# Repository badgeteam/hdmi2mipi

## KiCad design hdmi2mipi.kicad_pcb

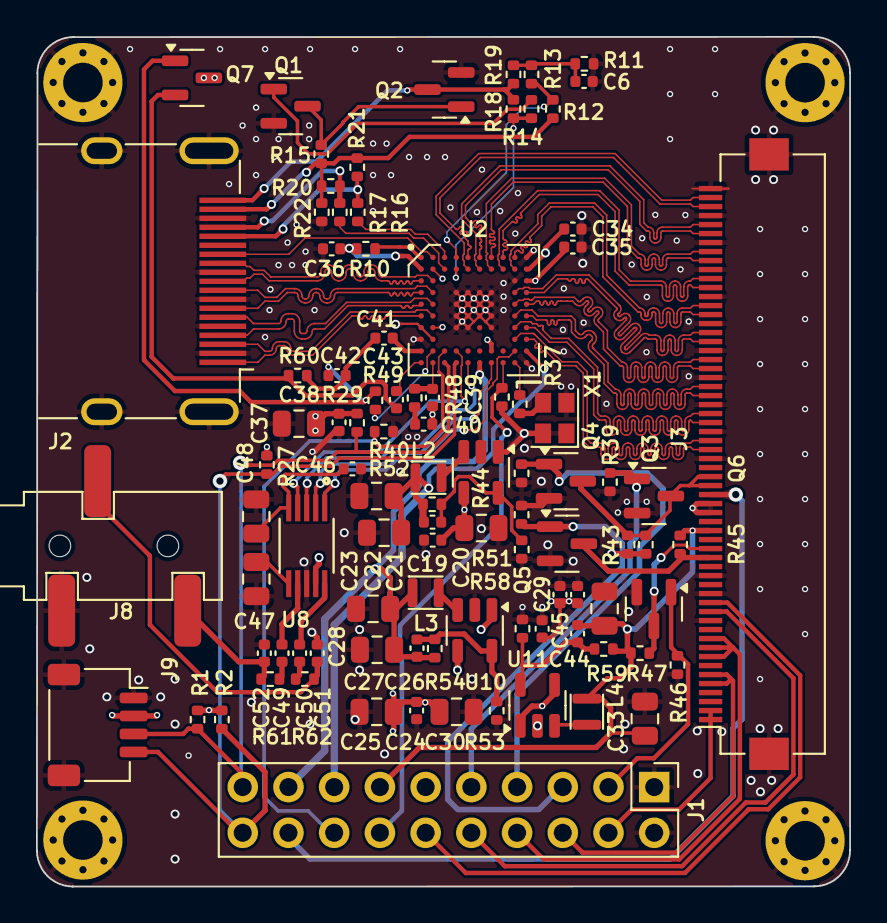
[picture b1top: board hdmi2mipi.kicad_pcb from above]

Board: 4 copper layers, 45.2 x 47.2 mm, 99 parts (0 on the bottom side), 91 nets.

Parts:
C6, C40, C41: 0.1u; C_0402_1005Metric
C19, C24, C29, C34, C35, C36, C38, C45, C46, C49, C50: 100n; C_0402_1005Metric
C20, C22, C23, C25, C27, C28, C30, C32, C33, C37: 22u; C_0805_2012Metric
C21, C26, C31: 22p; C_0402_1005Metric
C39, C43: 1n; C_0402_1005Metric
C42: 5p; C_0402_1005Metric
C44: 1u; C_0402_1005Metric
C47, C48: 47u; C_0805_2012Metric
C51, C52: 39n; C_0402_1005Metric
H1, H2, H3, H4: MountingHole_Pad; MountingHole_2.2mm_M2_Pad_Via
J1: IO; PinHeader_2x10_P2.54mm_Vertical
J2: HDMI_A_1.4; HDMI_A_Molex_208658-1001_Horizontal
J3: Hirose_FH52-60S-0.5SH_1x60-1MP_P0.50mm_Horizontal
J8: AudioJack3; Boom-audiojack-PJ-320B
J9: QWIIC; JST_SH_SM04B-SRSS-TB_1x04-1MP_P1.00mm_Horizontal
L2, L3, L4: 2.2u; Inductor_MSC20FC
Q1, Q2, Q3, Q4, Q5, Q6: BC846; SOT-23
Q7: 2SC2712; SOT-23
R1, R2, R10: 2k; R_0402_1005Metric
R11: 48k; R_0402_1005Metric
R12: 0; R_0402_1005Metric
R13, R49: 1.5k; R_0402_1005Metric
R14, R20, R21, R27, R29, R41, R43, R45, R47: 4.7k; R_0402_1005Metric
R15, R38, R39, R40, R42, R44, R46, R51, R52, R53, R58: 10k; R_0402_1005Metric
R16, R17, R37: 33; R_0402_1005Metric
R18, R19, R48, R60: 1k; R_0402_1005Metric
R22: 100k; R_0402_1005Metric
R54: 8.2k; R_0402_1005Metric
R59: 20k; R_0402_1005Metric
R61, R62: 330; R_0402_1005Metric
U2: tc358840xbg
U8: MS4344; SOP50P490X110-10N
U9, U10, U11: SY8079AAC; SOT-23-5
X1: SG-210STF; Oscillator_SMD_SeikoEpson_SG210-4Pin_2.5x2.0mm

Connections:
1V8_S1: J1.3, Q6.1 (B), R46.1
1V8_S2: J1.5, Q5.1 (B), R44.1
3V3_HDMI: C19.1, C20.1, C24.1, C25.1, C29.1, C30.1, C36.1, C37.1, C38.1, C44.1, C45.1, J1.11, J3.24 (3.3v), J3.25 (3.3v), J9.2, Q7.3 (C), R1.1, R2.1, R10.2, R27.1, R29.1, R38.1, R41.1, R43.1, U2.B1 (VDD33_HDMI), U2.G1 (VDD33_HDMI), U2.H2 (VDDIO33), U2.J7 (VDDIO18), U8.9 (VA), U9.1 (EN), U9.4 (VIN), U10.1 (EN), U10.4 (VIN), U11.1 (EN), U11.4 (VIN), X1.1 (~ST), X1.4 (Vcc)
3V3_S1: J1.7, Q4.1 (B), R42.1
3V3_S2: J1.9, Q3.1 (B), R39.1
+1V1: C26.1, C27.1, C28.1, C35.1, J1.17, L3.1, R54.1, U2.B2 (VDD11_HDMI), U2.C10 (VDDC11), U2.G2 (VDD11_HDMI), U2.K6 (VDDC11)
+1V2: C21.1, C22.1, C23.1, C34.1, J1.15, L2.1, R52.1, U2.B10 (VDD12_MIPI1), U2.J10 (VDD12_MIPI0)
+1V8: C31.1, C32.1, C33.1, J1.13, J3.22 (1.8v), L4.1, R45.1, R47.1, R59.1
/AUDIO_L: C52.2, J8.T, R61.2
/AUDIO_R: C51.2, J8.R, R62.2
/DSI0_C_N: J3.38 (DSI0CN), U2.F9 (CDSI0CN)
/DSI0_C_P: J3.37 (DSI0CP), U2.F10 (CDSI0CP)
/DSI0_D0_N: J3.32 (DSI0D0N), U2.H9 (CDSI0D0N)
/DSI0_D0_P: J3.31 (DSI0D0P), U2.H10 (CDSI0D0P)
/DSI0_D1_N: J3.35 (DSI0D1N), U2.G9 (CDSI0D1N)
/DSI0_D1_P: J3.34 (DSI0D1P), U2.G10 (CDSI0D1P)
/DSI0_D2_N: J3.41 (DSI0D2N), U2.E9 (CDSI0D2N)
/DSI0_D2_P: J3.40 (DSI0D2P), U2.E10 (CDSI0D2P)
/DSI0_D3_N: J3.44 (DSI0D3N), U2.D9 (CDSI0D3N)
/DSI0_D3_P: J3.43 (DSI0D3P), U2.D10 (CDSI0D3P)
/DSI1_C_N: J3.53 (DSI1CN), U2.B7 (CDSI1CN)
/DSI1_C_P: J3.52 (DSI1CP), U2.A7 (CDSI1CP)
/DSI1_D0_N: J3.47 (DSI1D0N), U2.B9 (CDSI1D0N)
/DSI1_D0_P: J3.46 (DSI1D0P), U2.A9 (CDSI1D0P)
/DSI1_D1_N: J3.50 (DSID1N), U2.B8 (CDSI1D1N)
/DSI1_D1_P: J3.49 (DSID1P), U2.A8 (CDSI1D1P)
/DSI1_D2_N: J3.56 (DSI1D2N), U2.B6 (CDSI1D2N)
/DSI1_D2_P: J3.55 (DSI1D2P), U2.A6 (CDSI1D2P)
/DSI1_D3_N: J3.59 (DSI1D3N), U2.B5 (CDSI1D3N)
/DSI1_D3_P: J3.58 (DSI1D3P), U2.A5 (CDSI1D3P)
/FB11: C26.2, R53.1, R54.2, U10.5 (FB)
/FB12: C21.2, R51.1, R52.2, U9.5 (FB)
/FB18: C31.2, R58.1, R59.2, U11.5 (FB)
/HDMI_0_N: J2.9 (D0-), U2.D2 (HDMID0N)
/HDMI_0_P: J2.7 (D0+), U2.D1 (HDMID0P)
/HDMI_1_N: J2.6 (D1-), U2.E2 (HDMID1N)
/HDMI_1_P: J2.4 (D1+), U2.E1 (HDMID1P)
/HDMI_2_N: J2.3 (D2-), U2.F2 (HDMID2N)
/HDMI_2_P: J2.1 (D2+), U2.F1 (HDMID2P)
/HDMI_C_N: J2.12 (CK-), U2.C2 (HDMICN)
/HDMI_C_P: J2.10 (CK+), U2.C1 (HDMICP)
/SW11: L3.2, U10.3 (SW)
/SW12: L2.2, U9.3 (SW)
/SW18: L4.2, U11.3 (SW)
GND: C6.2, C19.2, C20.2, C22.2, C23.2, C24.2, C25.2, C27.2, C28.2, C29.2, C30.2, C32.2, C33.2, C34.2, C35.2, C36.2, C37.2, C38.2, C39.2, C40.2, C44.2, C45.2, C46.2, C47.2, C48.2, C51.1, C52.1, H1.1, H2.1, H3.1, H4.1, J1.1, J1.2, J2.2 (D2S), J2.5 (D1S), J2.8 (D0S), J2.11 (CKS), J2.17 (GND), J2.SH, J3.12 (GND), J3.15 (GND), J3.17 (GND), J3.30 (GND), J3.33 (GND), J3.36 (GND), J3.39 (GND), J3.42 (GND), J3.45 (GND), J3.48 (GND), J3.51 (GND), J3.54 (GND), J3.57 (GND), J3.60 (GND), J3.MP, J8.S, J9.1, J9.MP (MountPin), Q1.2 (E), Q2.2 (E), Q3.2 (E), Q4.2 (E), Q5.2 (E), Q6.2 (E), R11.1, R22.1, R39.2, R40.2, R42.2, R44.2, R46.2, R51.2, R53.2, R58.2, U2.A10 (VSS), U2.C9 (VSS), U2.D4 (VSS), U2.D5 (VSS), U2.D6 (VSS), U2.D7 (VSS), U2.E4 (VSS), U2.E5 (VSS), U2.E6 (VSS), U2.E7 (VSS), U2.F4 (VSS), U2.F5 (VSS), U2.F6 (VSS), U2.F7 (VSS), U2.G4 (VSS), U2.G5 (TEST), U2.G7 (VSS), U2.H1 (VSS), U2.K10 (VSS), U8.8 (GND), U9.2 (GND), U10.2 (GND), U11.2 (GND), X1.2 (GND)
INT: J1.16, R40.1, U2.J3 (INT)
unnamed: C6.1, R11.2, R13.2, R19.2
unnamed: C40.1, R48.2
unnamed: C41.1, C42.2, R60.1
unnamed: C49.1, R61.1
unnamed: C50.2, R62.1
unnamed: J1.4, J3.1 (FB1), J3.2 (FB1)
unnamed: J1.6, J3.5 (FB2), J3.6 (FB2)
unnamed: J1.8, J3.8 (LED+), J3.9 (LED+), J3.10 (LED+)
unnamed: J1.10, J3.13 (5.8v-VEE)
unnamed: J1.12, J3.14 (5.8v-VDD)
unnamed: J2.18 (+5V), R12.1, R15.1, R20.1, R21.1, R22.2
unnamed: J2.13 (CEC), U2.A2 (CEC)
unnamed: J2.19 (HPD/HEAC-), Q2.3 (C), R18.2, R19.1
unnamed: J2.15 (SCL), R16.2, R21.2
unnamed: J2.16 (SDA), R17.1, R20.2
unnamed: J3.20 (1.8-S1), Q6.3 (C), R47.2
unnamed: J3.19 (1.8-S2), Q5.3 (C), R45.2
unnamed: J3.27 (3.3-S2), J3.28 (3.3-S1), Q3.3 (C), Q4.3 (C), R41.2, R43.2
unnamed: Q1.1 (B), R14.1
unnamed: Q1.3 (C), Q2.1 (B), R15.2
unnamed: C42.1, Q7.1 (B), R49.1
unnamed: C43.1, Q7.2 (E), R60.2
unnamed: U2.J4 (A_OSCK), U8.4 (MCLK)
unnamed: U2.K7 (A_SCK), U8.2 (~DEM/SCLK)
unnamed: U2.J9 (A_SD0), U8.1 (SDIN)
unnamed: U2.K5 (A_WFS), U8.3 (LRCK)
unnamed: C41.2, U2.J1 (BIASDA)
unnamed: R49.2, U2.J2 (DAOUT)
unnamed: R16.1, U2.A3 (DDC_SCL)
unnamed: R17.2, U2.B3 (DDC_SDA)
unnamed: R12.2, R13.1, U2.A4 (HPDI)
unnamed: R14.2, R18.1, U2.B4 (HPDO)
unnamed: C43.2, U2.K1 (PCKIN)
unnamed: C39.1, R48.1, U2.K2 (PFIL)
unnamed: R37.2, U2.K9 (REFCLK)
unnamed: R10.1, U2.A1 (REXT)
unnamed: C49.2, U8.7 (AOUTL)
unnamed: C50.1, U8.10 (AOUTR)
unnamed: C47.1, U8.6 (FILT+)
unnamed: C46.1, C48.1, U8.5 (VQ)
unnamed: R37.1, X1.3 (OUT)
RESET: J1.14, R38.2, U2.K8 (~RESET)
SCL: J1.20, J9.4, R2.2, R27.2, U2.K4 (I2C_SCL)
SDA: J1.19, J9.3, R1.2, R29.2, U2.K3 (I2C_SDA)
VIN: J1.18, J3.26 (5v)

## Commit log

2024-02-22 Simplify and get ready for component placement and routing
2024-02-27 tracing done
2024-02-28 labels ordering
2024-02-29 changed layout
2024-03-02 made smaller board
2024-03-03 Small fixes and combine 2.54mm headers
2024-03-05 Fixed some routing issues and a bunch of DRC rule violations. Set the board setup to JLCPCB constraints.
2024-03-06 Changed copper layers, heaps of other issues.
2024-03-07 Fixed many warnings and errors.
2024-03-29 Last tweaks and order at JLC

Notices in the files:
hdmi2mipi.kicad_pcb:
CERN-OHL-P
